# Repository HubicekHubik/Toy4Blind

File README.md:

# Toy4Blind
Documentation of batchelors project on CTU FEE. Theme of the project is to create toy taht motivates blind child to move/crowl around the room using haptic and sound feedback. Toy is powerd by xiao nrf52840 sense which is programed via NRF connect for VS

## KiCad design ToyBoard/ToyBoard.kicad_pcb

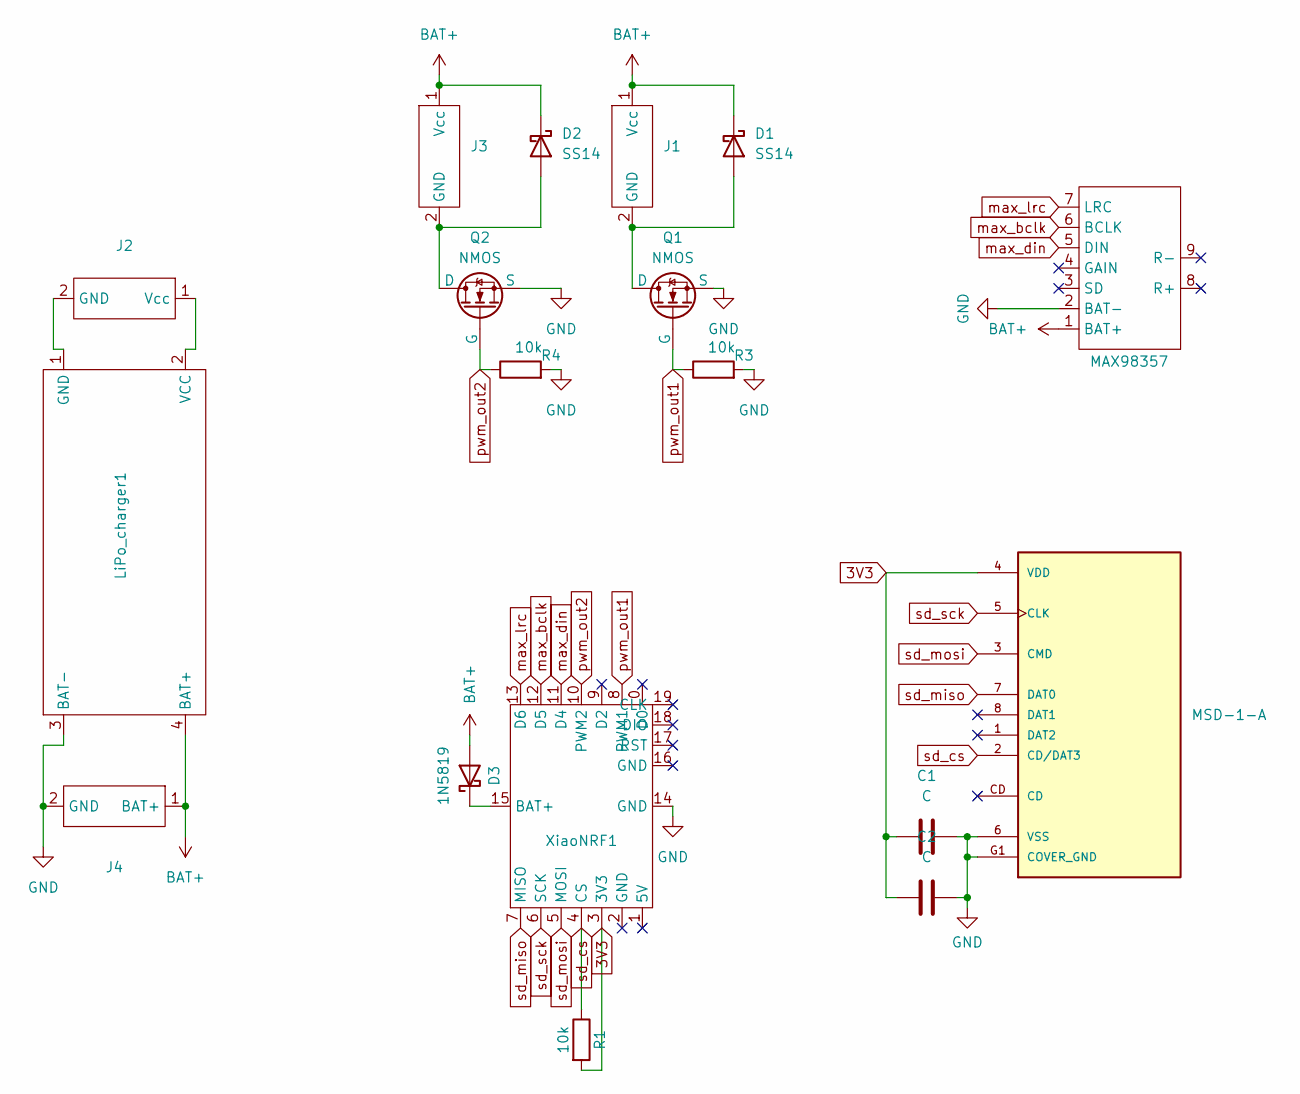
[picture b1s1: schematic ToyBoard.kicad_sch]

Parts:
C1, C2: C; C_0402_1005Metric_Pad0.74x0.62mm_HandSolder
D1, D2: SS14; D_SMA
D3: 1N5819; D_DO-41_SOD81_P10.16mm_Horizontal
J1, J2, J3, J4: JST_My
J5: MSD-1-A; CUI_MSD-1-A; PARTREV 1.0
LiPo_charger1: Lipolchargerfoot
MAX98357: MAX98357Footprint
Q1, Q2: NMOS; TSOT-23
R1, R3, R4: 10k; R_0805_2012Metric_Pad1.20x1.40mm_HandSolder
XiaoNRF1: XiaoTrace

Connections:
3V3: C1.1, C2.1, J5.4 (VDD), R1.2, XiaoNRF1.3 (3V3)
BAT+: D1.1 (K), D2.1 (K), D3.2 (A), J1.1 (Vcc), J3.1 (Vcc), J4.1 (BAT+), LiPo_charger1.4 (BAT+), MAX98357.1 (BAT+)
GND: C1.2, C2.2, J4.2 (GND), J5.6 (VSS), J5.G1 (COVER_GND), J5.G2 (COVER_GND), J5.G3 (COVER_GND), J5.G4 (COVER_GND), LiPo_charger1.3 (BAT-), MAX98357.2 (BAT-), Q1.3 (S), Q2.3 (S), R3.2, R4.2, XiaoNRF1.14 (GND)
unnamed: D1.2 (A), J1.2 (GND), Q1.1 (D)
unnamed: D2.2 (A), J3.2 (GND), Q2.1 (D)
unnamed: D3.1 (K), XiaoNRF1.15 (BAT+)
unnamed: J2.2 (GND), LiPo_charger1.1 (GND)
unnamed: J2.1 (Vcc), LiPo_charger1.2 (VCC)
max_bclk: MAX98357.6 (BCLK), XiaoNRF1.12 (D5)
max_din: MAX98357.5 (DIN), XiaoNRF1.11 (D4)
max_lrc: MAX98357.7 (LRC), XiaoNRF1.13 (D6)
pwm_out1: Q1.2 (G), R3.1, XiaoNRF1.8 (PWM1)
pwm_out2: Q2.2 (G), R4.1, XiaoNRF1.10 (PWM2)
sd_cs: J5.2 (CD/DAT3), R1.1, XiaoNRF1.4 (CS)
sd_miso: J5.7 (DAT0), XiaoNRF1.7 (MISO)
sd_mosi: J5.3 (CMD), XiaoNRF1.5 (MOSI)
sd_sck: J5.5 (CLK), XiaoNRF1.6 (SCK)

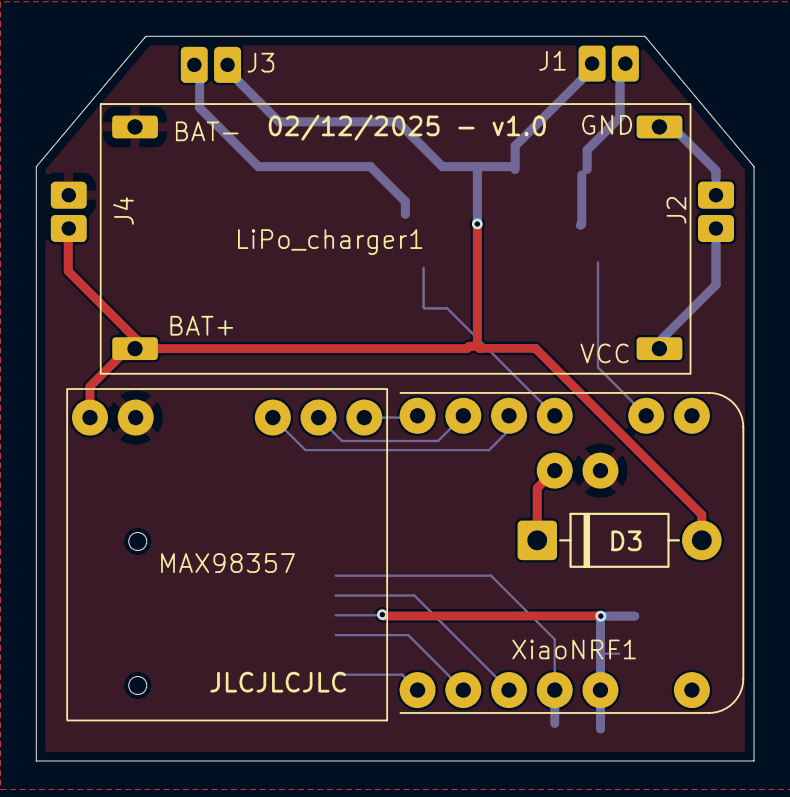
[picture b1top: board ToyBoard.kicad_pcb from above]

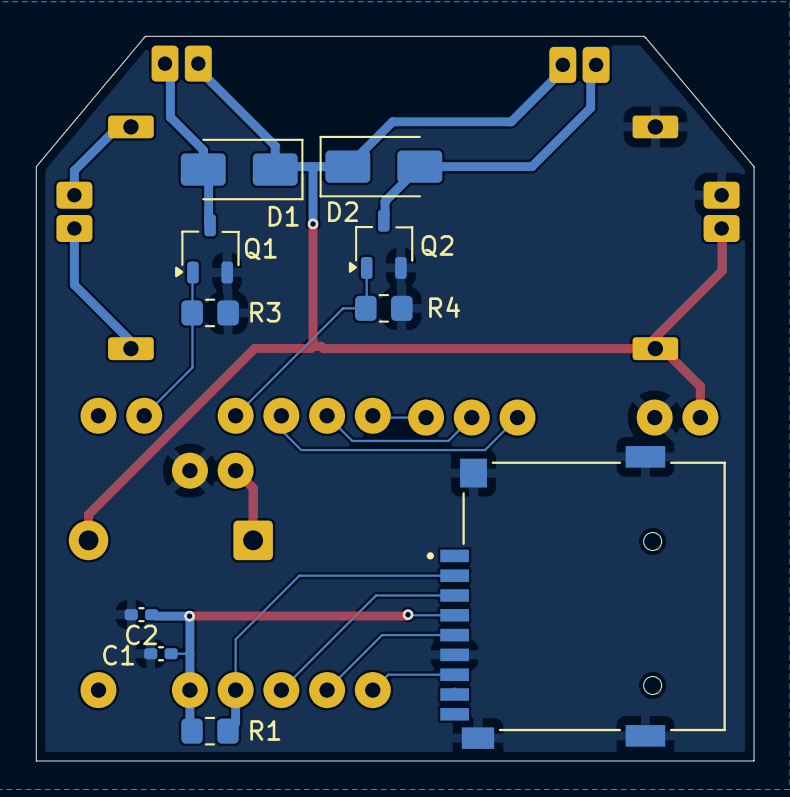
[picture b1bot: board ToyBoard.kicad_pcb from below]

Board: 4 copper layers, 39.9 x 40.3 mm, 18 parts (10 on the bottom side), 17 nets.

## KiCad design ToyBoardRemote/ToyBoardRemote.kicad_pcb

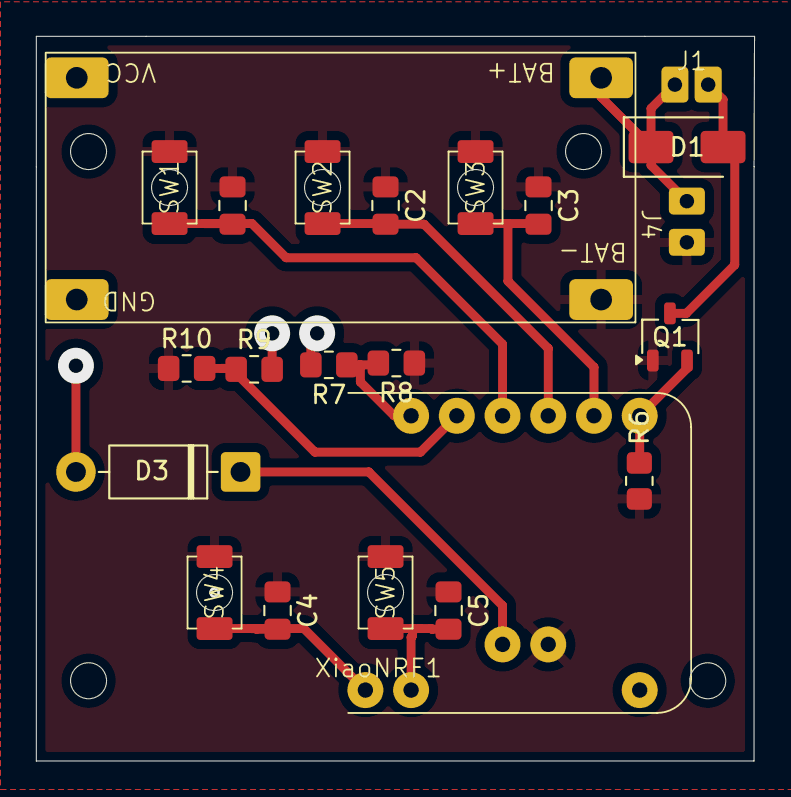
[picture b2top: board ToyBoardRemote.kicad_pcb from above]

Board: 4 copper layers, 39.9 x 40.3 mm, 22 parts (0 on the bottom side), 12 nets.

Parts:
C1, C2, C3, C4, C5: C; C_0805_2012Metric_Pad1.18x1.45mm_HandSolder
D1: SS14; D_SMA
D3: 1N5819; D_DO-41_SOD81_P10.16mm_Horizontal
J1, J4: JST_My
Q1: NMOS; TSOT-23
R6: 10k; R_0805_2012Metric_Pad1.20x1.40mm_HandSolder
R7, R9: 470k; R_0805_2012Metric_Pad1.20x1.40mm_HandSolder
R8, R10: 1M; R_0805_2012Metric_Pad1.20x1.40mm_HandSolder
SW1, SW2, SW3, SW4, SW5: SW_Push; SMD_ SW 3x4x2
U1: Lipolchargerfoot
XiaoNRF1: XiaoTrace

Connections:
BAT+: D1.1 (K), D3.2 (A), J1.1 (Vcc), J4.1 (BAT+), U1.4 (BAT+)
GND: C1.1, C2.1, C3.1, C4.1, C5.1, J4.2 (GND), Q1.3 (S), R6.2, R8.1, R10.1, SW1.2, SW2.2, SW3.2, SW4.2, SW5.2, U1.3 (BAT-), XiaoNRF1.14 (GND)
unnamed: D1.2 (A), J1.2 (GND), Q1.1 (D)
unnamed: D3.1 (K), XiaoNRF1.15 (BAT+)
unnamed: Q1.2 (G), R6.1, XiaoNRF1.0 (D0)
unnamed: C2.2, SW2.1, XiaoNRF1.9 (D2)
unnamed: R9.1, R10.2, XiaoNRF1.11 (D4)
unnamed: R7.1, R8.2, XiaoNRF1.12 (D5)
unnamed: C3.2, SW3.1, XiaoNRF1.8 (PWM1)
unnamed: C1.2, SW1.1, XiaoNRF1.10 (PWM2)
unnamed: C4.2, SW4.1, XiaoNRF1.7 (RX)
unnamed: C5.2, SW5.1, XiaoNRF1.6 (SCK)

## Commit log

2025-11-28 Project Toy4Blind adding kicad circ, fusion 360 model and all codes
2025-12-12 Pcb and Gerbs for JLCPCB
2025-12-12 Wireless code for EI data acquisition
2025-12-12 Main code for Toy and Toyremote
2025-12-12 test programs
2025-12-12 Codes used for testing, data acq and main
2025-12-12 pages
2025-12-12 added docs for git pages
2026-02-11 beforeADClpcomp
2026-03-24 cleanup
2026-03-25 pagesupdate
2026-03-25 pages update
2026-03-30 ADC init inspiration
2026-03-30 nvs inspiration
2026-03-30 New web
2026-03-30 old pages delete
2026-04-02 web update
2026-04-03 Separated evaluation from result_ready_cb
2026-04-03 repaired On/Off func for remote and phone compatibility
2026-04-03 edited max namber of category
2026-04-03 Added struct for classifier data
2026-04-03 removed coments
2026-04-03 added long press for bt disconnect
2026-04-03 wiring rework
2026-04-10 app battery icons and xml
2026-04-10 script change for magnitude training
2026-04-10 added powinf send to app
2026-04-10 removed big battery class and added smaller pow class
2026-04-10 changed classes added comands
2026-04-10 reworked bataery alerts to be only module dependent
2026-04-10 added effects
2026-04-10 changed sampling freq saperated gest evlaluation form call back
2026-04-10 increased talk back campatibility
2026-04-10 added battery indication
2026-04-10 new sound
2026-04-10 repaired after ble connection remote crash
2026-04-10 battery info to app related changes
2026-04-10 magnitude based CNN classifier
2026-04-10 remove old class
2026-04-22 updated for easier navigation and 2 devices conection
2026-04-22 deleted sounds
2026-04-22 added sounds for category change feedback
2026-04-22 new sounds for chain mode
2026-04-22 sys changes feedback sounds
2026-04-22 new sounds
2026-04-22 changed for chain mode
2026-04-22 add ignore thesis
2026-04-22 added and changed effects
2026-04-22 changed draw audio and addedpermute and find
2026-04-22 added game mode in to saves
2026-04-22 added game modul for chains game mode
2026-04-22 reordered added gamemodul
2026-04-22 added crash handling
2026-04-22 adid crash handling and tx power
2026-04-22 adjusted and added effects
2026-04-22 revorked rx audio event handling
2026-04-22 revorked press events
2026-04-22 aded power status inf oin mat state msg
2026-04-22 aded MSG types and reworked event structures
2026-04-22 chnaged speed handling and characteristic subscription
2026-04-22 revorked calback and calssification results handling
2026-04-22 addid states handling
2026-04-22 aded low bat haptic signalization
2026-05-08 cleared schem
2026-05-18 cleaner schematic
